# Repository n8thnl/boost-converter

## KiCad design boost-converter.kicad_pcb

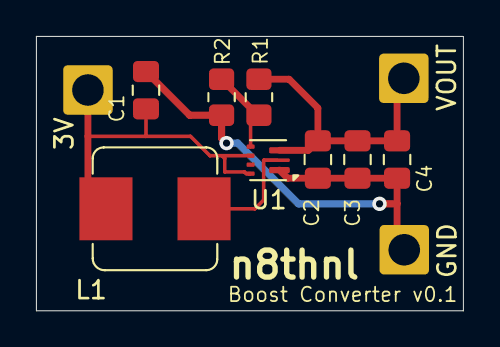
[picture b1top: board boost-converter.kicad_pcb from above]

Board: 2 copper layers, 23.7 x 15.2 mm, 11 parts (0 on the bottom side), 5 nets.

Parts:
3V: SolderWire-1sqmm_1x01_D1.4mm_OD2.7mm
C1: 10uF; C_0805_2012Metric_Pad1.18x1.45mm_HandSolder
C2, C3, C4: 22uF; C_0805_2012Metric_Pad1.18x1.45mm_HandSolder
GND: SolderWire-1sqmm_1x01_D1.4mm_OD2.7mm
L1: 1.0uH; L_Bourns_SRP7028A_7.3x6.6mm
R1: 732k; R_0805_2012Metric_Pad1.20x1.40mm_HandSolder
R2: 100k; R_0805_2012Metric_Pad1.20x1.40mm_HandSolder
U1: TPS61022; Texas_RWU0007A_VQFN-7_2x2mm_P0.5mm
VOUT: SolderWire-1sqmm_1x01_D1.4mm_OD2.7mm

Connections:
+3V: 3V.1, C1.1, L1.1, U1.5 (EN), U1.7 (VIN)
+5V: C2.2, C3.2, C4.2, R1.1, U1.3 (VOUT), VOUT.1
GND: C1.2, C2.1, C3.1, C4.1, GND.1, R2.2, U1.1 (GND)
unnamed: R1.2, R2.1, U1.4 (FB)
unnamed: L1.2, U1.2 (SW)

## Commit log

2024-04-30 Create LICENSE
